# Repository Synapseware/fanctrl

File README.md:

Fan Controller
==============

Computer case fan speed controller, which uses a simple "fixed" buck converter for controller fan voltage.

PWM is not ideal for DC brushless fans, especially if you want to get constant data from the speed sensor.  This circuit forms a very simple buck converter by using a high-switching frequency coupled with the standard inductor, capacitor and diode.

# ADC Input
The ADC is configured for free-running mode.  The input to the ADC should pass through an RC filter or an RLC filter for improved noise immunity.

## Input Pin
The ADC is configured to read from PB4.

## ADC Sense Line
The input to the ADC should be constrained to 0.0v through 1.1v.  This gives the most accuracy on the ADC and allows for a small load/sense resistor.

# PWM Output
Timer1 is used in a Fast-PWM configuration with the 64mHz PLL clock.  This allows for a maximum of 250kHz switching frequency.  Relatively low by today's standards but very workable on a proto board or hand-made board.

## PWM Output Pin
The PWM output is available on PB1.  The output should not be filtered since it must be fed to the SMPS switching element.  Care should be taken to keep this line short and include an appropriately sized pull-down/pull-up resistor to ensure safe operation of the power MOSFET or other switching transistor.

# Other Chip Information
The AVR uC is configured to use it's internal R/C oscillator.  High clock accuracy is not needed by this circuit and keeping the part count low is a goal of this example.

# Build
This project compiles and uploads just fine using Linux and avr-gnu.

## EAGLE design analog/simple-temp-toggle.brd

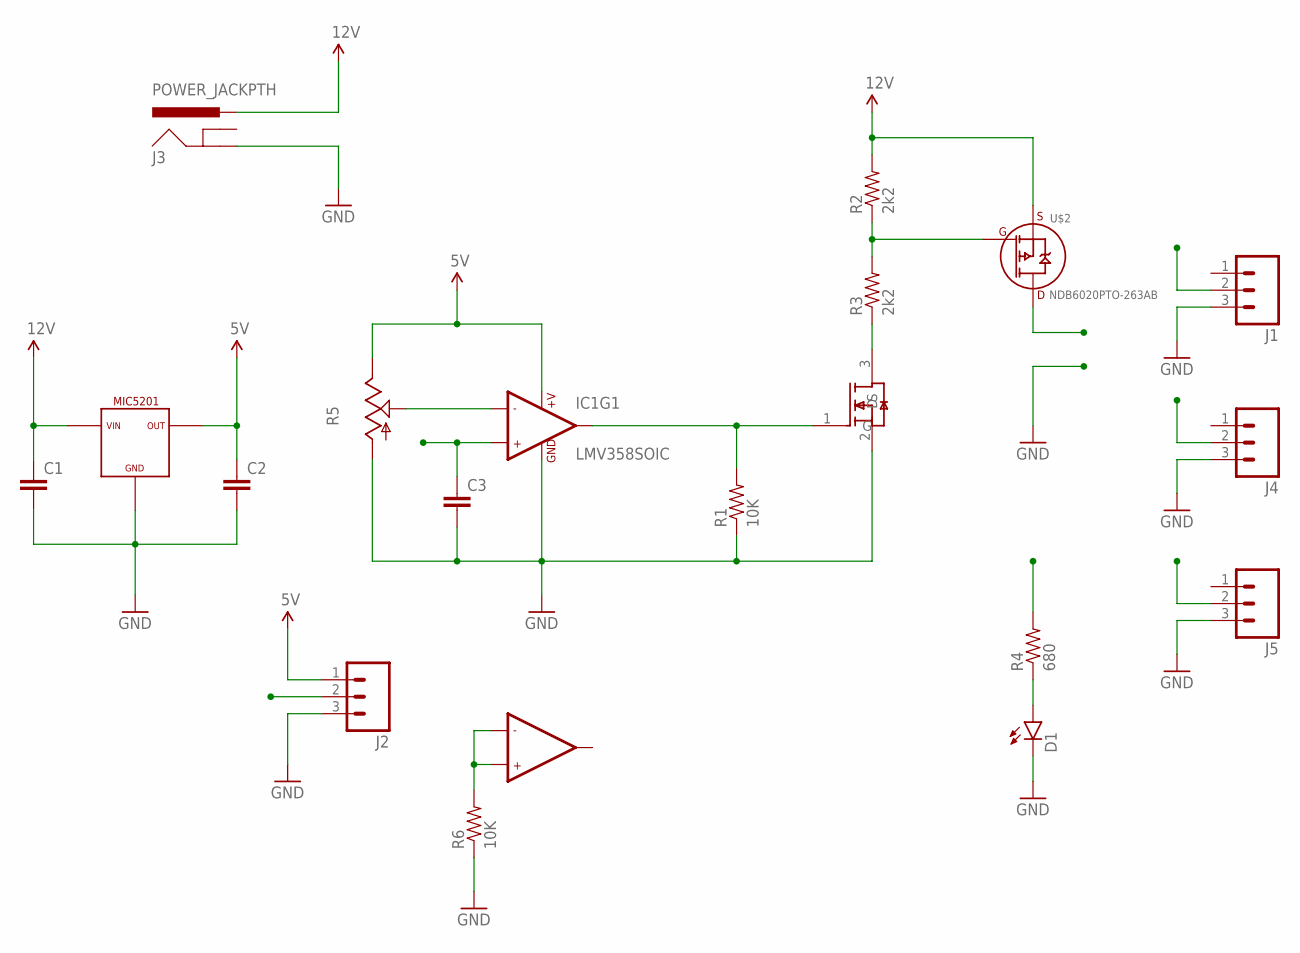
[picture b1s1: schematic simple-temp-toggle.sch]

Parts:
C1, C2, C3: 2.2UF50V10%(1206); 1206-CAP
D1: LED-FKIT-1206; FKIT-LED-1206
IC1: LMV358SOIC; SO08
J1, J2, J4, J5: M03LONGPADS; 1X03_LONGPADS
J3: POWER_JACKPTH; POWER_JACK_PTH
R1, R6: 10K; 1206
R2, R3: 2k2; 1206
R4: 680; 1206
R5: TRIM_US-S64W; S64W
U$2: NDB6020PTO-263AB; TO-263AB
U$3: MIC5201SOT-223; SOT-223
U$4: DMG2302UKSOT-23-3; SOT-23-3

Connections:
5V: C2.1, IC1.8 (+V), J2.1, R5.E, U$3.3 (OUT)
12V: C1.1, J3.PWR, R2.2, U$2.3 (S), U$3.1 (IN)
FAN_CTRL: IC1.1 (OUT1), R1.2, U$4.1 (G)
FAN_PWR: J1.2, J4.2, J5.2, R4.2, U$2.4 (D)
GND: C1.2, C2.2, C3.2, D1.C, IC1.4 (GND), J1.3, J2.3, J3.GND, J4.3, J5.3, R1.1, R5.A, R6.1, U$3.2 (GND), U$4.2 (S)
unnamed: IC1.2 (-IN1), R5.S
unnamed: IC1.5 (+IN2), IC1.6 (-IN2), R6.2
unnamed: D1.A, R4.1
unnamed: R2.1, R3.2, U$2.1 (G)
unnamed: R3.1, U$4.3 (D)
TMP_SENSOR: C3.1, IC1.3 (+IN1), J2.2

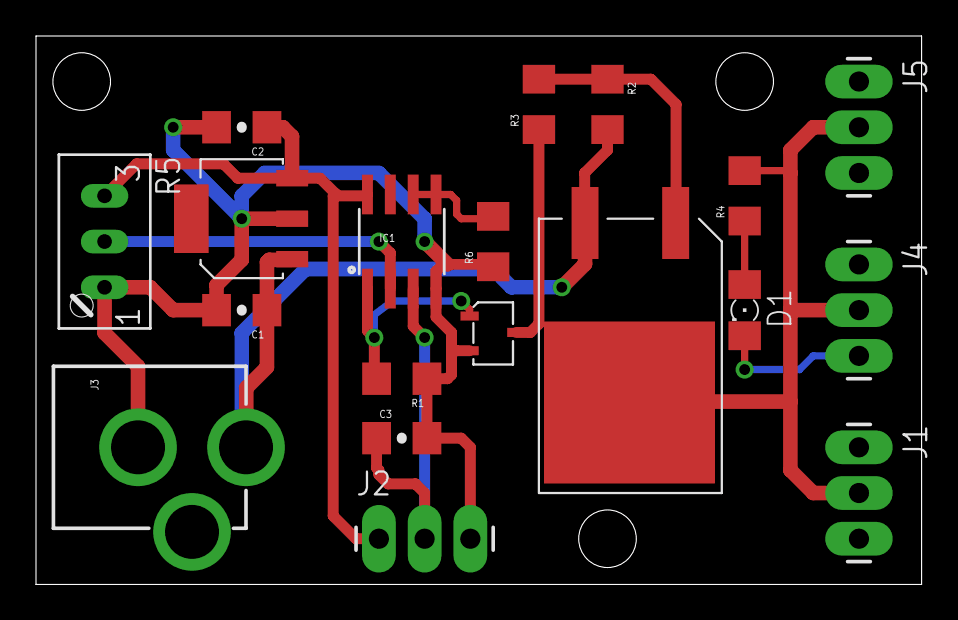
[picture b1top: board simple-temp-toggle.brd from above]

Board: 2 copper layers, 49.2 x 30.5 mm, 19 parts (0 on the bottom side), 11 nets.

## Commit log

2016-09-25 Adding template project files
2016-09-25 Moving files
2016-09-25 Rename
2016-09-25 Working on PWM frequency & config
2016-09-27 Updates for the fan controller
2017-02-12 Updating the fancontroller
2017-02-12 Initial draft of fan controller
    There's probably a MUCH easier way to do this, but it's fun.
2017-02-13 Converting to use ATMega168
    Too many problems with the Tiny85: timers, interrupts, SPI, etc.
2017-02-13 ATMega168 version is mostly functional
    Transform function(s) not yet implemented, so there's no conversion from
    external temp sensor to control the fan speed.
2017-02-23 WIP: Not sending correct data to the digital resistor
    The circuit works, the ADC works, but it's not sending the correct data
    to the MCP4131-103 (a 10k digital potentiometer). Next up, is to write
    canned data.
2017-08-18 Catchup
2017-08-18 Eagle update
2018-01-05 Capturing protoboard layout
2019-09-16 Analog fan controller
2019-11-23 Board updates
2019-11-23 New temp board

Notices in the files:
parts and their libraries:
SparkFun-Capacitors: Licensing: Creative Commons ShareAlike 4.0 International - https://creativecommons.org/licenses/by-sa/4.0
